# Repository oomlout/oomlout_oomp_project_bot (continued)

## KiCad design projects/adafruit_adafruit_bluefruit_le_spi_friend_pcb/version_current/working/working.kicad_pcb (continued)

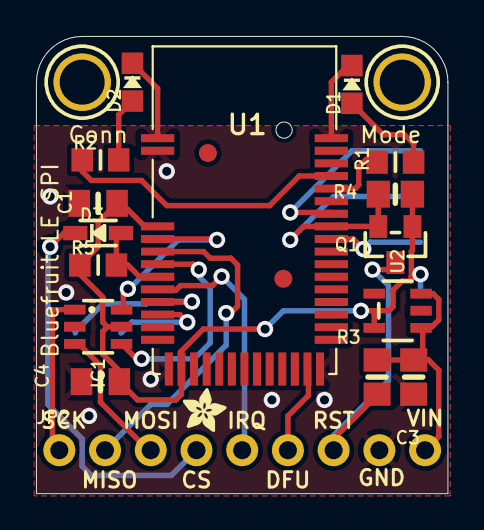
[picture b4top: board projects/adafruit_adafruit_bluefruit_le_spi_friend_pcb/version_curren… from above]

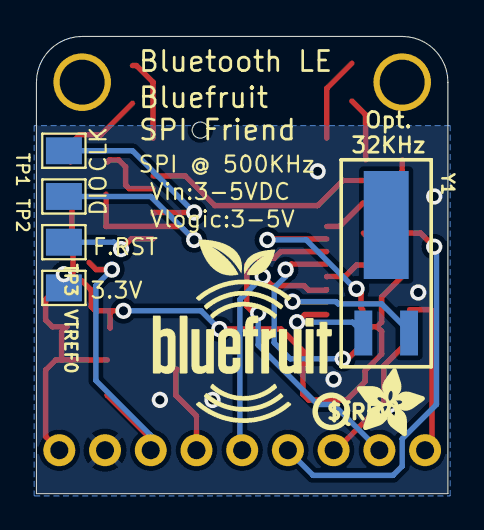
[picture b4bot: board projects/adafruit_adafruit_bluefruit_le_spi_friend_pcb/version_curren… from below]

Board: 2 copper layers, 22.9 x 25.4 mm, 29 parts (8 on the bottom side), 22 nets.

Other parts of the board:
U$3: ADAFRUIT_2.5MM
U$9: BLUEFRUITLOGO_100MM
U$17: ADAFRUIT_3.5MM
U$18: PCBFEAT-REV-040

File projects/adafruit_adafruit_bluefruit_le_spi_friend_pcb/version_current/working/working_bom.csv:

Row,Description,Part,References,Value,Footprint,Quantity Per PCB,Status,Datasheet
1,,CAP_CERAMIC0805_10MGAP,C1,1uF,0805_10MGAP,1, ,
2,,CAP_CERAMIC0805-NOOUTLINE,C3,10uF,0805-NO,1, ,
3,,CAP_CERAMIC0805_10MGAP,C4,10uF,0805_10MGAP,1, ,
4,,DIODESOD-323,D3,1N4148,SOD-323,1, ,
5,,LED0805_NOOUTLINE,D2,BLUE,CHIPLED_0805_NOOUTLINE,1, ,
6,,LED0805_NOOUTLINE,D1,RED,CHIPLED_0805_NOOUTLINE,1, ,
7,,74LVC2G34DBVR,IC1,74LVC2G34DBVR,SOT23-6,1, ,
8,,HEADER-1X970MIL,JP2,HEADER-1X970MIL,1X09_ROUND_70,1, ,
9,,MOSFET-NWIDE,Q1,BSS138,SOT23-WIDE@1,1, ,
10,,RESISTOR_0805MP,R1 R2,2K,_0805MP,2, ,
11,,RESISTOR0805_NOOUTLINE,R3 R4,100K,0805-NO,2, ,
12,,RESISTOR_0805MP,R5,100K,_0805MP,1, ,
13,,NRF51822_MODULE_MDBT40,U1,32KB NRF51822,BLE_MODULE_RAYTAC_MDBT40,1, ,
14,,VREG_SOT23-5,U2,MIC5225-3.3,SOT23-5,1, ,
15,,CRYSTAL2.0X6.0_32.768,Y1,32.768kHz (535-9166-2-ND),CRYSTAL_CYL_2X6MM_SMT,1, ,





Project info:
Schematic:,working
Variant:,default
Revision:,
Date:,2023-08-02_17-08-32
KiCad Version:,7.0.6-7.0.6~ubuntu22.04.1
Statistics:
Component Groups:,15
Component Count:,17 (0 SMD/ 0 THT)
Fitted Components:,17 (0 SMD/ 0 THT)
Number of PCBs:,1
Total Components:,17

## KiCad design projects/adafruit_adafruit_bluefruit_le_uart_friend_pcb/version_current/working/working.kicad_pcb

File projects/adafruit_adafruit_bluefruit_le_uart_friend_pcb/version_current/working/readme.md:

# OOMP Project  
## Adafruit-Bluefruit-LE-UART-Friend-PCB  by adafruit  
  
oomp key: oomp_projects_flat_adafruit_adafruit_bluefruit_le_uart_friend_pcb  
(snippet of original readme)  
  
- Adafruit Bluefruit LE UART Friend PCB  
<a href="http://www.adafruit.com/products/2479"><br/>  
Click here to purchase one from the Adafruit shop</a>  
  
The Bluefruit LE UART Friend makes it easy to add Bluetooth Low Energy connectivity to anything with a hardware or software serial port. We even have nice hardware flow control so you won't have to think about losing data. Connect to your Arduino or other microcontroller or even just a standard FTDI cable for debugging and testing.  
  
This multi-function module can do quite a lot! For most people, they'll be very happy to use the standard Nordic UART RX/TX connection profile. In this profile, the Bluefruit acts as a data pipe, that can 'transparently' transmit back and forth from your iOS or Android device. You can use our iOS App or Android App, or write your own to communicate with the UART service.  
  
PCB files for Adafruit Bluefruit LE UART Friend. Format is EagleCAD.   
- https://www.adafruit.com/product/2479  
  
--- License  
  
Adafruit invests time and resources providing this open source design, please support Adafruit and open-source hardware by purchasing products from [Adafruit](https://www.adafruit.com)!  
  
All text above must be included in any redistribution  
  
Designed by Limor Fried/Ladyada for Adafruit Industries.  
Creative Commons Attribution/Share-Alike, all text above must be included in any redistribution.   
See license.txt for additional information.  
  
  full source readme at [readme_src.md](readme_src.md)  
  
source repo at: [https://github.com/adafruit/Adafruit-Bluefruit-LE-UART-Friend-PCB](https://github.com/adafruit/Adafruit-Bluefruit-LE-UART-Friend-PCB)  
## Board  

## Schematic  

[schematic pdf](working_schematic.pdf)  
## Images

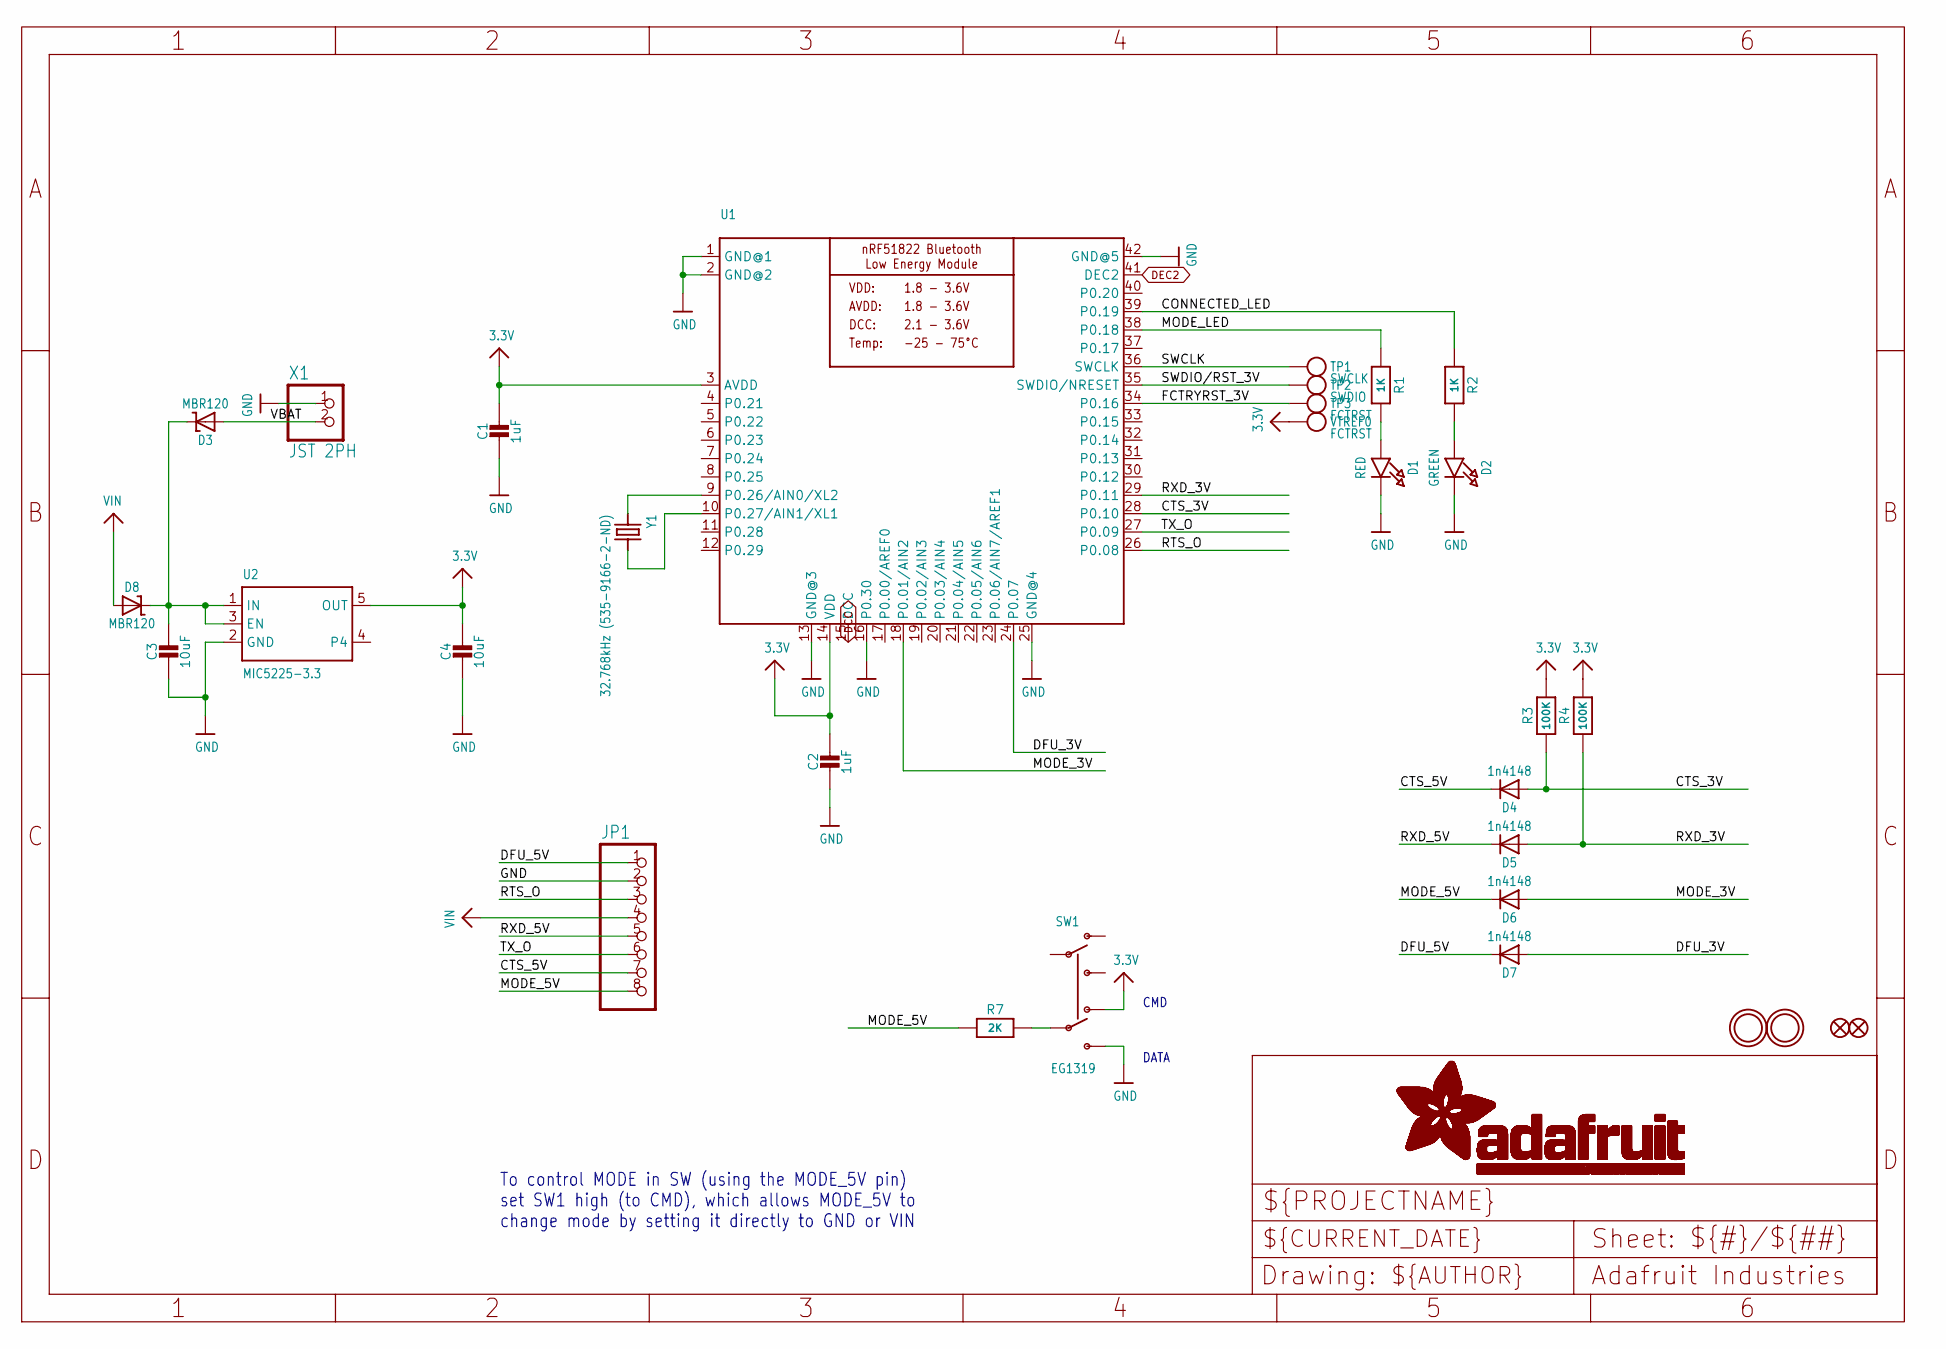
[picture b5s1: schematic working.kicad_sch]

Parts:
C1, C2: 1uF; 0805-NO
C3, C4: 10uF; 0805-NO
D1: RED; CHIPLED_0805_NOOUTLINE
D2: GREEN; CHIPLED_0805_NOOUTLINE
D3, D8: MBR120; SOD-123
D4, D5, D6, D7: 1n4148; SOD-323
FID1, FID2: FIDUCIAL""; FIDUCIAL_1MM
JP1: HEADER-1X876MIL; 1X08_ROUND_76
R1, R2: 1K; 0805-NO
R3, R4: 100K; 0805-NO
R7: 2K; 0805-NO
SW1: EG1319; EG1390
TP1: SWCLK; PAD-1.5X2.0
TP2: SWDIO; PAD-1.5X2.0
TP3: FCTRST; PAD-1.5X2.0
U1: NRF51822_MODULE_MDBT40; BLE_MODULE_RAYTAC_MDBT40
U2: MIC5225-3.3; SOT23-5
U$28, U$29: MOUNTINGHOLE2.5; MOUNTINGHOLE_2.5_PLATED
VTREF0: FCTRST; PAD-1.5X2.0
X1: JST 2PH; JSTPH2
Y1: 32.768kHz (535-9166-2-ND); CRYSTAL_CYL_2X6MM_SMT

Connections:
3.3V: C1.1, C2.1, C4.1, R3.2, R4.2, SW1.O2, U1.3 (AVDD), U1.14 (VDD), U2.5 (OUT), VTREF0.P$1
CONNECTED_LED: R2.1, U1.39 (P0.19)
CTS_3V: D4.A, R3.1, U1.28 (P0.10)
CTS_5V: D4.C, JP1.7
DCC: U1.15 (DCC)
DEC2: U1.41 (DEC2)
DFU_3V: D7.A, U1.24 (P0.07)
DFU_5V: D7.C, JP1.1
FCTRYRST_3V: TP3.P$1, U1.34 (P0.16)
GND: C1.2, C2.2, C3.2, C4.2, D1.C, D2.C, JP1.2, SW1.S2, U1.1 (GND@1), U1.2 (GND@2), U1.13 (GND@3), U1.16 (P0.30), U1.25 (GND@4), U1.42 (GND@5), U2.2 (GND), X1.1
MODE_3V: D6.A, U1.18 (P0.01/AIN2)
MODE_5V: D6.C, JP1.8, R7.1
MODE_LED: R1.1, U1.38 (P0.18)
unnamed: U1.9 (P0.26/AIN0/XL2), Y1.1
unnamed: U1.10 (P0.27/AIN1/XL1), Y1.2
unnamed: C3.1, D3.C, D8.C, U2.1 (IN), U2.3 (EN)
unnamed: R7.2, SW1.P2
unnamed: D1.A, R1.2
unnamed: D2.A, R2.2
RTS_O: JP1.3, U1.26 (P0.08)
RXD_3V: D5.A, R4.1, U1.29 (P0.11)
RXD_5V: D5.C, JP1.5
SWCLK: TP1.P$1, U1.36 (SWCLK)
SWDIO/RST_3V: TP2.P$1, U1.35 (SWDIO/NRESET)
TX_O: JP1.6, U1.27 (P0.09)
VBAT: D3.A, X1.2
VIN: D8.A, JP1.4

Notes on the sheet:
To control MODE in SW (using the MODE_5V pin) set SW1 high (to CMD), which allows MODE_5V to change mode by setting it directly to GND or VIN
CMD
DATA

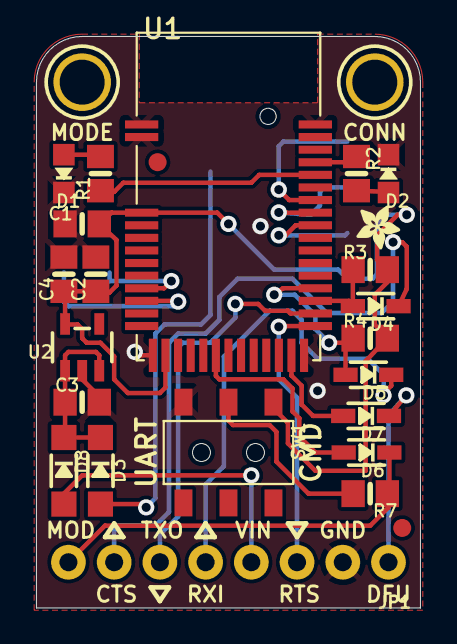
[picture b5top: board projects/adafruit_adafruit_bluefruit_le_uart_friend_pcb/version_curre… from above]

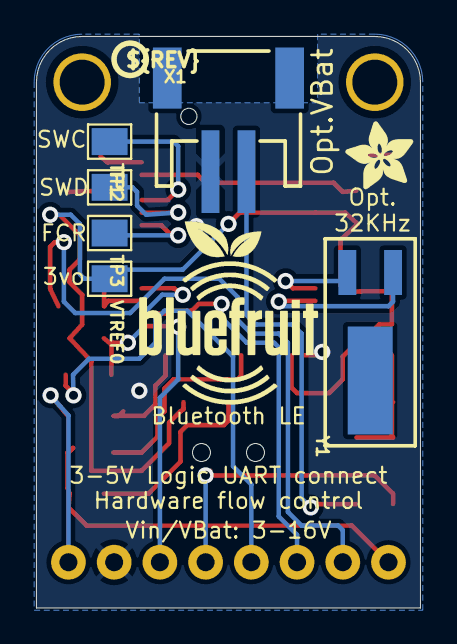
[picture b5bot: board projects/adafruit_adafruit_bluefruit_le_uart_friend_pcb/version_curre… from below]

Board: 2 copper layers, 21.3 x 31.8 mm, 35 parts (9 on the bottom side), 25 nets.

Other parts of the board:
U$9: BLUEFRUITLOGO_100MM
U$24: PCBFEAT-REV-040
U$25: ADAFRUIT_3.5MM
U$26: ADAFRUIT_2.5MM

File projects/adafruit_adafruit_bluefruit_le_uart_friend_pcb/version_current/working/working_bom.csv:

Row,Description,Part,References,Value,Footprint,Quantity Per PCB,Status,Datasheet
1,,CAP_CERAMIC0805-NOOUTLINE,C1 C2,1uF,0805-NO,2, ,
2,,CAP_CERAMIC0805-NOOUTLINE,C3 C4,10uF,0805-NO,2, ,
3,,DIODESOD-323,D4 D5 D6 D7,1n4148,SOD-323,4, ,
4,,LED0805_NOOUTLINE,D2,GREEN,CHIPLED_0805_NOOUTLINE,1, ,
5,,DIODE-SCHOTTKYSOD-123,D3 D8,MBR120,SOD-123,2, ,
6,,LED0805_NOOUTLINE,D1,RED,CHIPLED_0805_NOOUTLINE,1, ,
7,,HEADER-1X876MIL,JP1,HEADER-1X876MIL,1X08_ROUND_76,1, ,
8,,RESISTOR0805_NOOUTLINE,R1 R2,1K,0805-NO,2, ,
9,,RESISTOR0805_NOOUTLINE,R7,2K,0805-NO,1, ,
10,,RESISTOR0805_NOOUTLINE,R3 R4,100K,0805-NO,2, ,
11,,SWITCH_DPDTEG1390,SW1,EG1319,EG1390,1, ,
12,,VREG_SOT23-5,U2,MIC5225-3.3,SOT23-5,1, ,
13,,NRF51822_MODULE_MDBT40,U1,NRF51822_MODULE_MDBT40,BLE_MODULE_RAYTAC_MDBT40,1, ,
14,,CON_JST_PH_2PIN,X1,JST 2PH,JSTPH2,1, ,
15,,CRYSTAL2.0X6.0_32.768,Y1,32.768kHz (535-9166-2-ND),CRYSTAL_CYL_2X6MM_SMT,1, ,





Project info:
Schematic:,working
Variant:,default
Revision:,
Date:,2023-08-02_17-08-32
KiCad Version:,7.0.6-7.0.6~ubuntu22.04.1
Statistics:
Component Groups:,15
Component Count:,23 (0 SMD/ 0 THT)
Fitted Components:,23 (0 SMD/ 0 THT)
Number of PCBs:,1
Total Components:,23

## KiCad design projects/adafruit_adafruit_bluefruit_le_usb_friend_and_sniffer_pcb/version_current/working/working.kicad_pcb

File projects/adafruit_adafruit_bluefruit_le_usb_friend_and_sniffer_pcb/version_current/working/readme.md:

# Adafruit-Bluefruit-LE-USB-Friend-and-Sniffer-PCB by adafruit  
This is a harvested standardized copy of a project from github.  
The original project can be found at:  
https://github.com/adafruit/Adafruit-Bluefruit-LE-USB-Friend-and-Sniffer-PCB  
Please consult that link for additional, details, files, and license information.  
Note: It was auto harvested and if the original repo had more than one board file or anything out of the ordinary the files here are likely not representative.

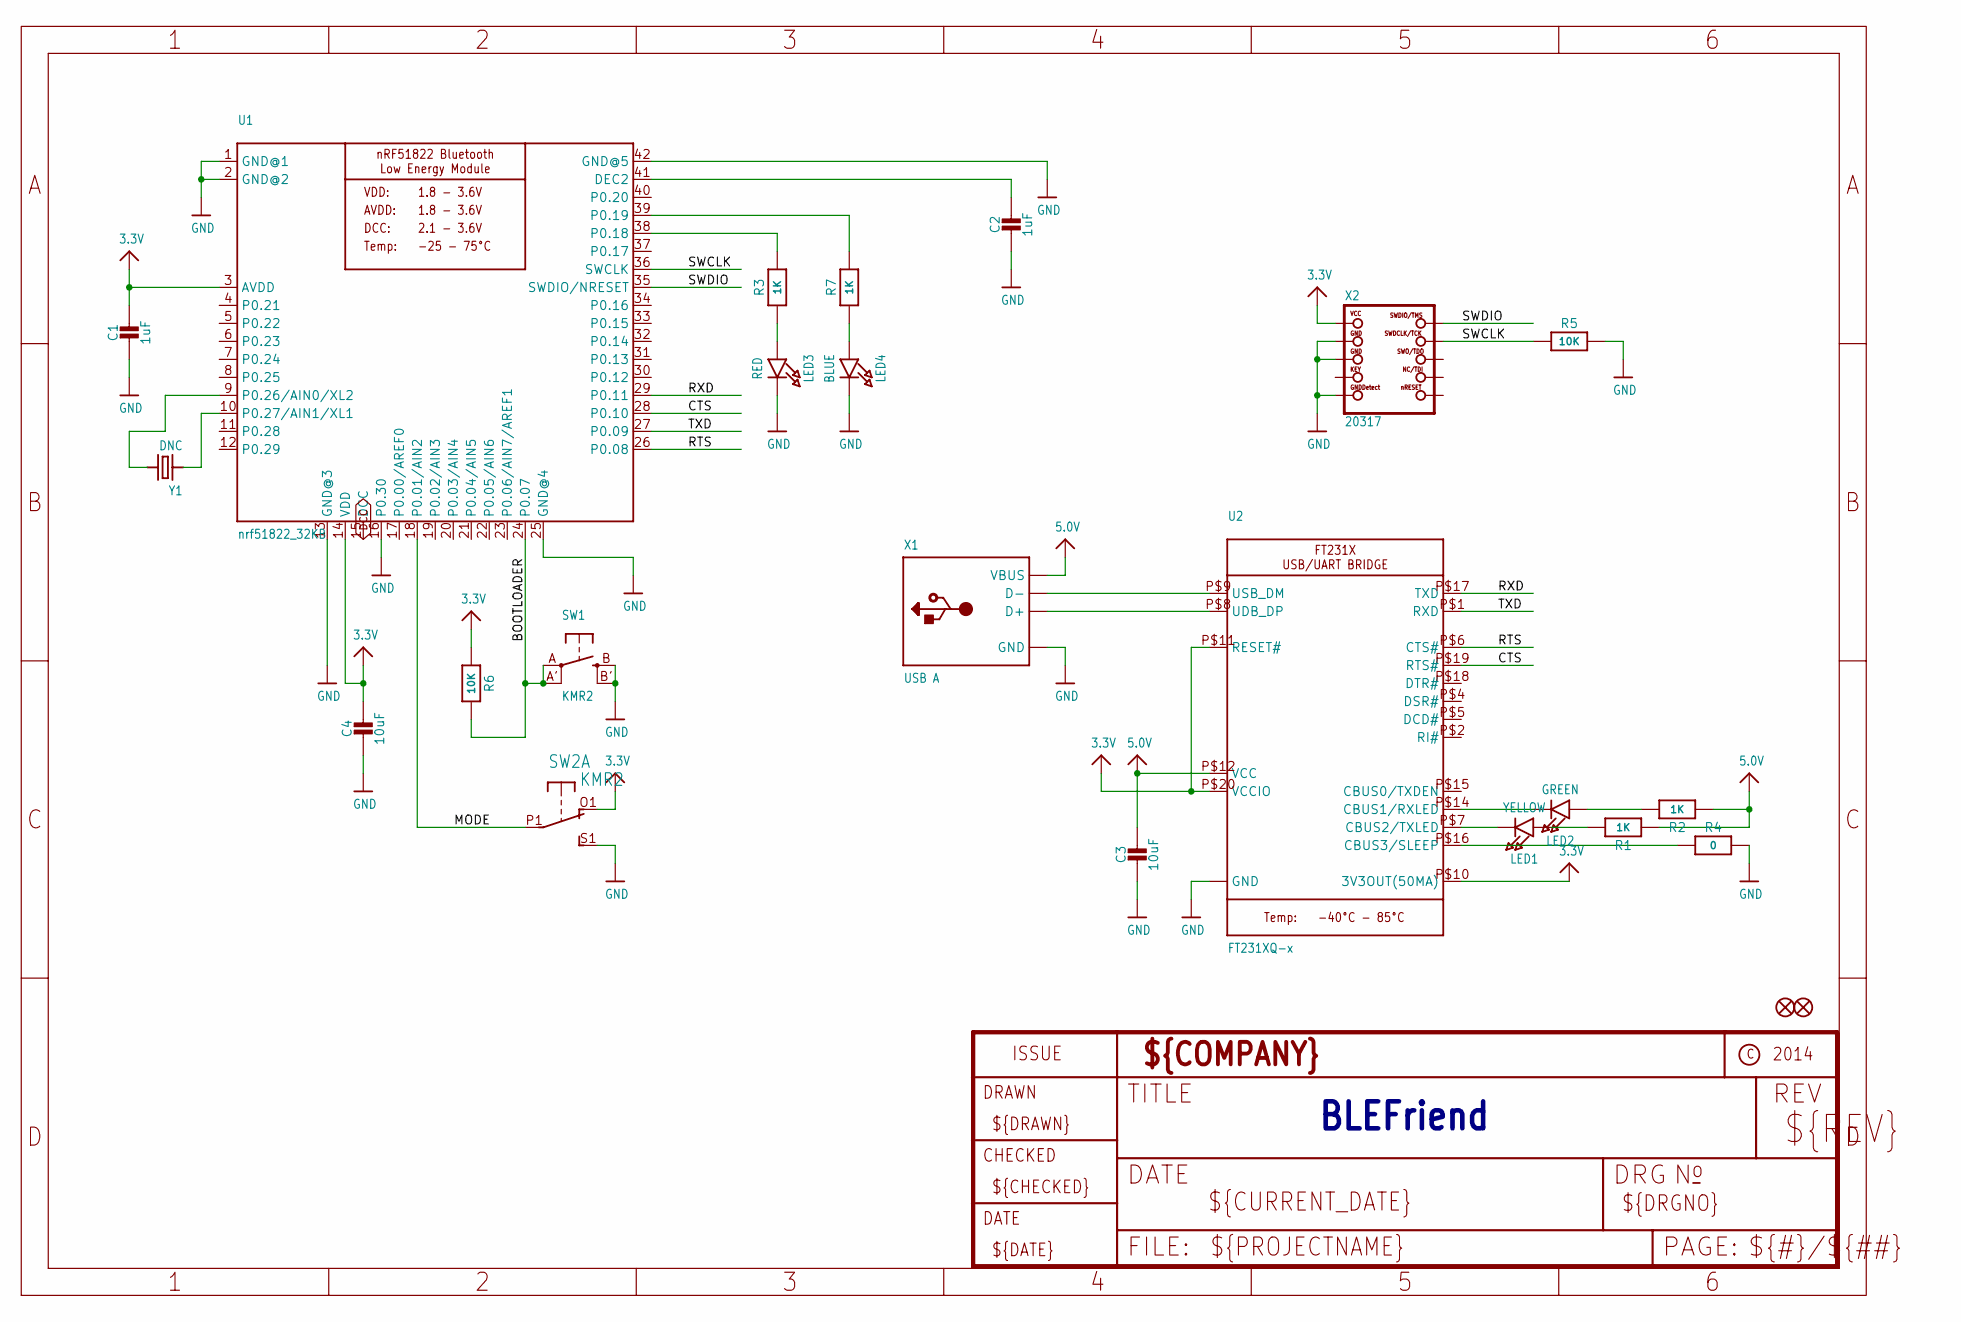
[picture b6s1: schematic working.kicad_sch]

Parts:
C1, C2: 1uF; _0805MP
C3, C4: 10uF; _0805MP
FID1, FID2: FIDUCIAL""; FIDUCIAL_1MM
LED1: YELLOW; CHIPLED_0805_NOOUTLINE
LED2: GREEN; CHIPLED_0805_NOOUTLINE
LED3: RED; CHIPLED_0805_NOOUTLINE
LED4: BLUE; CHIPLED_0805_NOOUTLINE
R1, R2, R3, R7: 1K; _0805MP
R4: 0; _0805MP
R5, R6: 10K; _0805MP
SW1: KMR2; BTN_KMR2_4.6X2.8
SW2: KMR2; EG1390
U1: nrf51822_32KB; BLE_MODULE_RAYTAC_MDBT40
U2: FT231XQ-x; QFN20_4MM
X1: USB A; USB_A-THM
X2: 20317; 2X05_1.27MM_BOX_POSTS
Y1: DNC; CRYSTAL_CYL_2X6MM_SMT

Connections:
3.3V: C1.1, C4.1, R6.1, SW2.O1 (O), U1.3 (AVDD), U1.14 (VDD), U2.P$10 (3V3OUT(50MA)), U2.P$11 (RESET#), U2.P$20 (VCCIO), X2.1 (VCC)
5.0V: C3.1, R1.1, R2.1, U2.P$12 (VCC), X1.VBUS
BOOTLOADER: R6.2, SW1.A, SW1.A' (P1), U1.24 (P0.07)
CTS: U1.28 (P0.10), U2.P$19 (RTS#)
DCC: U1.15 (DCC)
GND: C1.2, C2.2, C3.2, C4.2, LED3.C, LED4.C, R4.2, R5.2, SW1.B (S), SW1.B' (S1), SW2.S1 (S), U1.1 (GND@1), U1.2 (GND@2), U1.13 (GND@3), U1.16 (P0.30), U1.25 (GND@4), U1.42 (GND@5), U2.P$3 (GND), U2.P$13 (GND), U2.P$21 (GND), X1.GND, X2.3 (GND@1), X2.5 (GND@2), X2.9 (GNDDETECT)
MODE: SW2.P1, U1.18 (P0.01/AIN2)
unnamed: LED2.A, R2.2
unnamed: C2.1, U1.41 (DEC2)
unnamed: LED3.A, R3.1
unnamed: LED1.A, R1.2
unnamed: LED1.C, U2.P$7 (CBUS2/TXLED)
unnamed: LED2.C, U2.P$14 (CBUS1/RXLED)
unnamed: R4.1, U2.P$16 (CBUS3/SLEEP)
unnamed: U2.P$8 (UDB_DP), X1.D+
unnamed: U2.P$9 (USB_DM), X1.D-
unnamed: R3.2, U1.38 (P0.18)
unnamed: R7.2, U1.39 (P0.19)
unnamed: LED4.A, R7.1
unnamed: U1.9 (P0.26/AIN0/XL2), Y1.2
unnamed: U1.10 (P0.27/AIN1/XL1), Y1.1
RTS: U1.26 (P0.08), U2.P$6 (CTS#)
RXD: U1.29 (P0.11), U2.P$17 (TXD)
SWCLK: R5.1, U1.36 (SWCLK), X2.4 (SWDCLK)
SWDIO: U1.35 (SWDIO/NRESET), X2.2 (SWDIO)
TXD: U1.27 (P0.09), U2.P$1 (RXD)

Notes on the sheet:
BLEFriend

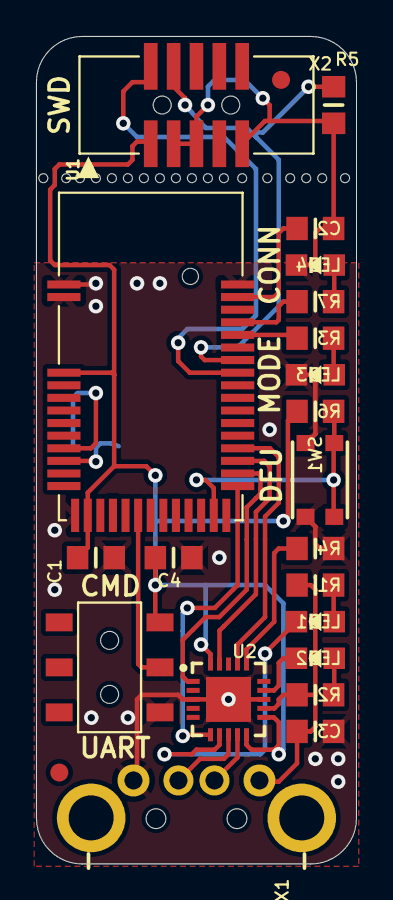
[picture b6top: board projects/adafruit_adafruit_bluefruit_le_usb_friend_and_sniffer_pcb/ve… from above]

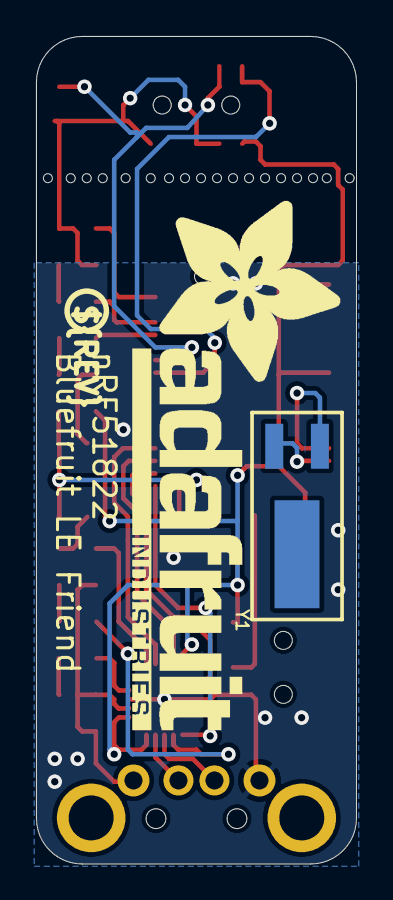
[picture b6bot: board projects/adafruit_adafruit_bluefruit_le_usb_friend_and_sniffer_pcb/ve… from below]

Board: 2 copper layers, 17.8 x 46.0 mm, 44 parts (3 on the bottom side), 25 nets.

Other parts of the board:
@HOLE0, @HOLE1, @HOLE2, @HOLE3, @HOLE4, @HOLE5, @HOLE6, @HOLE7, @HOLE8, @HOLE9, @HOLE10, @HOLE11, @HOLE12, @HOLE13, @HOLE14, @HOLE15, @HOLE16, @HOLE17: (no value)
U$22: ADAFRUIT_TEXT_30MM
U$27: PCBFEAT-REV-056

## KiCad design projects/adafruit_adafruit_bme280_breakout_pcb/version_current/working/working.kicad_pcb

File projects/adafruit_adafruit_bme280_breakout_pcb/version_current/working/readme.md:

# Adafruit-BME280-Breakout-PCB by adafruit  
This is a harvested standardized copy of a project from github.  
The original project can be found at:  
https://github.com/adafruit/Adafruit-BME280-Breakout-PCB  
Please consult that link for additional, details, files, and license information.  
Note: It was auto harvested and if the original repo had more than one board file or anything out of the ordinary the files here are likely not representative.

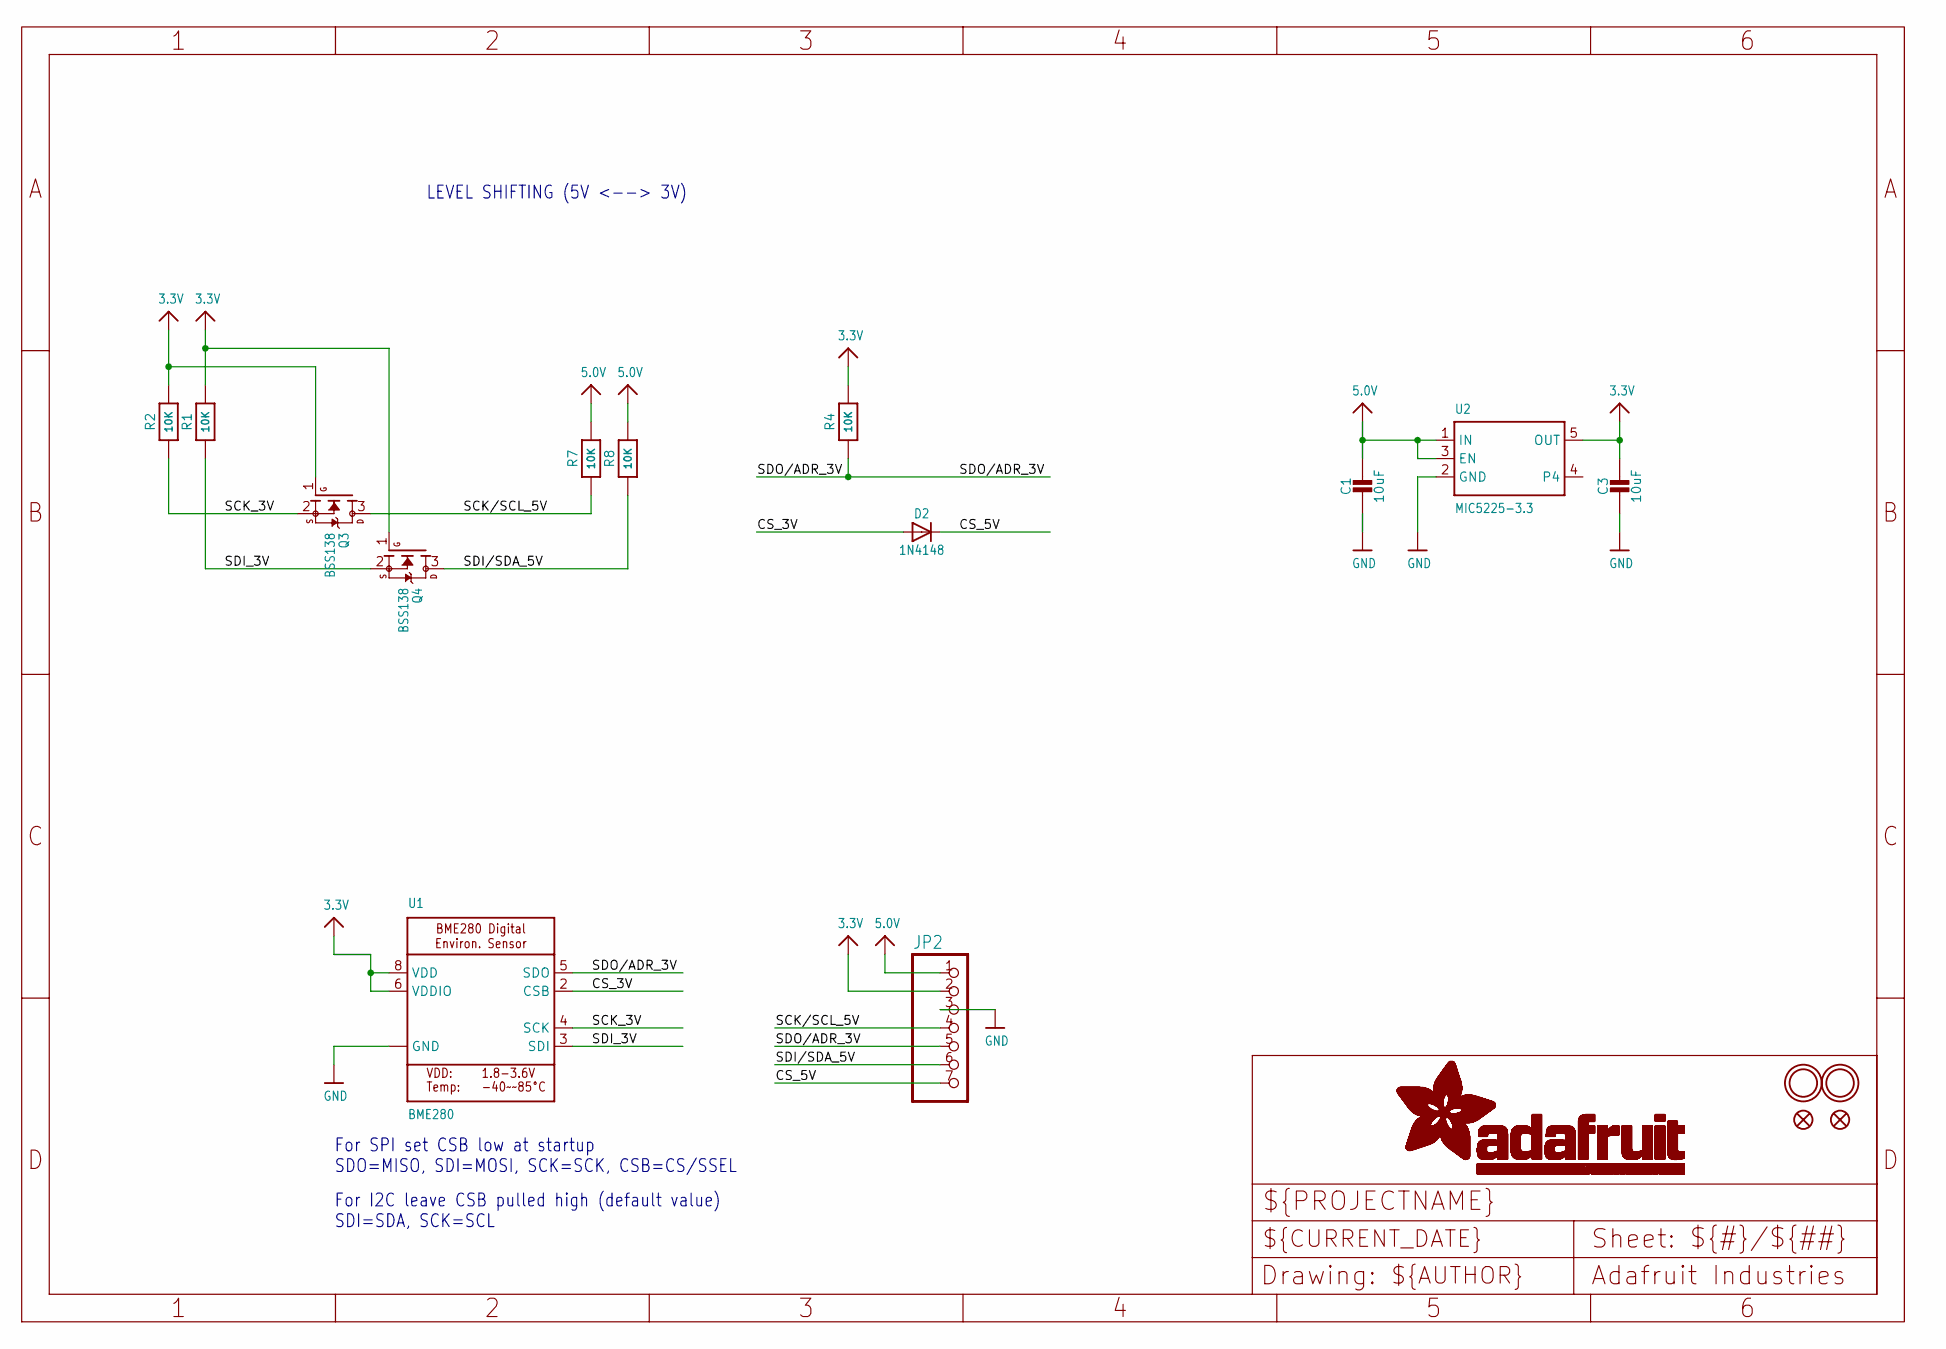
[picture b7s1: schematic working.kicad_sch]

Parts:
C1, C3: 10uF; 0805-NO
D2: 1N4148; SOD-323
JP2: HEADER-1X770MIL; 1X07_ROUND_70
Q3, Q4: BSS138; SOT23-WIDE
R1, R2, R7, R8: 10K; 0805-NO
R4: 10K; _0805MP
U1: BME280
U2: MIC5225-3.3; SOT23-5
U$5, U$15: FIDUCIAL""; FIDUCIAL_1MM
U$7, U$8: MOUNTINGHOLE2.0; MOUNTINGHOLE_2.0_PLATED

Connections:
3.3V: C3.1, JP2.2, Q3.1 (G), Q4.1 (G), R1.2, R2.2, R4.2, U1.6 (VDDIO), U1.8 (VDD), U2.5 (OUT)
5.0V: C1.1, JP2.1, R7.2, R8.2, U2.1 (IN), U2.3 (EN)
CS_3V: D2.A, U1.2 (CSB)
CS_5V: D2.C, JP2.7
GND: C1.2, C3.2, JP2.3, U1.1 (GND), U1.7 (GND), U2.2 (GND)
SCK/SCL_5V: JP2.4, Q3.3 (D), R7.1
SCK_3V: Q3.2 (S), R2.1, U1.4 (SCK)
SDI/SDA_5V: JP2.6, Q4.3 (D), R8.1
SDI_3V: Q4.2 (S), R1.1, U1.3 (SDI)
SDO/ADR_3V: JP2.5, R4.1, U1.5 (SDO)

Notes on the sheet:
LEVEL SHIFTING (5V <--> 3V)
For SPI set CSB low at startup SDO=MISO, SDI=MOSI, SCK=SCK, CSB=CS/SSEL
For I2C leave CSB pulled high (default value) SDI=SDA, SCK=SCL

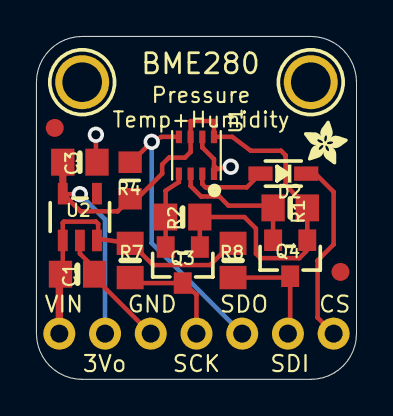
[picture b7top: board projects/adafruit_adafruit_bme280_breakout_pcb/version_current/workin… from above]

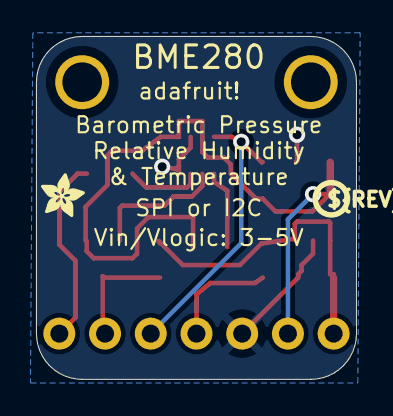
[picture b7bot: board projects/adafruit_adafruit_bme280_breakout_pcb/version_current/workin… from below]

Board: 2 copper layers, 17.8 x 19.0 mm, 20 parts (2 on the bottom side), 10 nets.

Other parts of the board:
U$2, U$6: ADAFRUIT_2.5MM
U$20: PCBFEAT-REV-040

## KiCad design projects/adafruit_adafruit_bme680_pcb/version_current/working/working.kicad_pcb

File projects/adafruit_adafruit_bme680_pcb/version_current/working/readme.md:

# OOMP Project  
## Adafruit-BME680-PCB  by adafruit  
  
oomp key: oomp_projects_flat_adafruit_adafruit_bme680_pcb  
(snippet of original readme)  
  
-- Adafruit BME680 PCB  
  
<a href="http://www.adafruit.com/products/3660"><br/>  
Click here to purchase one from the Adafruit shop</a>  
  
PCB files for the Adafruit BME680 Breakout. Format is EagleCAD schematic and board layout  
  
For more details, check out the product page at  
* https://www.adafruit.com/product/3660  
  
--- Description  
  
The long awaited BME680 from Bosch gives you all the environmental sensing you want in one small package. This little sensor contains temperature, humidity, barometric pressure, and VOC gas sensing capabilities. All over SPI or I2C at a great price!  
  
Like the BME280 & BMP280, this precision sensor from Bosch can measure humidity with ±3% accuracy, barometric pressure with ±1 hPa absolute accuracy, and temperature with ±1.0°C accuracy. Because pressure changes with altitude, and the pressure measurements are so good, you can also use it as an altimeter with  ±1 meter or better accuracy!  
  
The BME680 takes those sensors to the next step in that it contains a small MOX sensor. The heated metal oxide changes resistance based on the volatile organic compounds (VOC) in the air, so it can be used to detect gasses & alcohols such as Ethanol, Alcohol and Carbon Monoxide, and perform air quality measurements. Note it will give you one resistance value, with overall VOC content, but it cannot differentiate gasses or alcohols.  
  
Please note this sensor, like all VOC/gas sensors, has variability and to get precise me  
  full source readme at [readme_src.md](readme_src.md)  
  
source repo at: [https://github.com/adafruit/Adafruit-BME680-PCB](https://github.com/adafruit/Adafruit-BME680-PCB)  
## Board  

## Schematic  

[schematic pdf](working_schematic.pdf)  
## Images

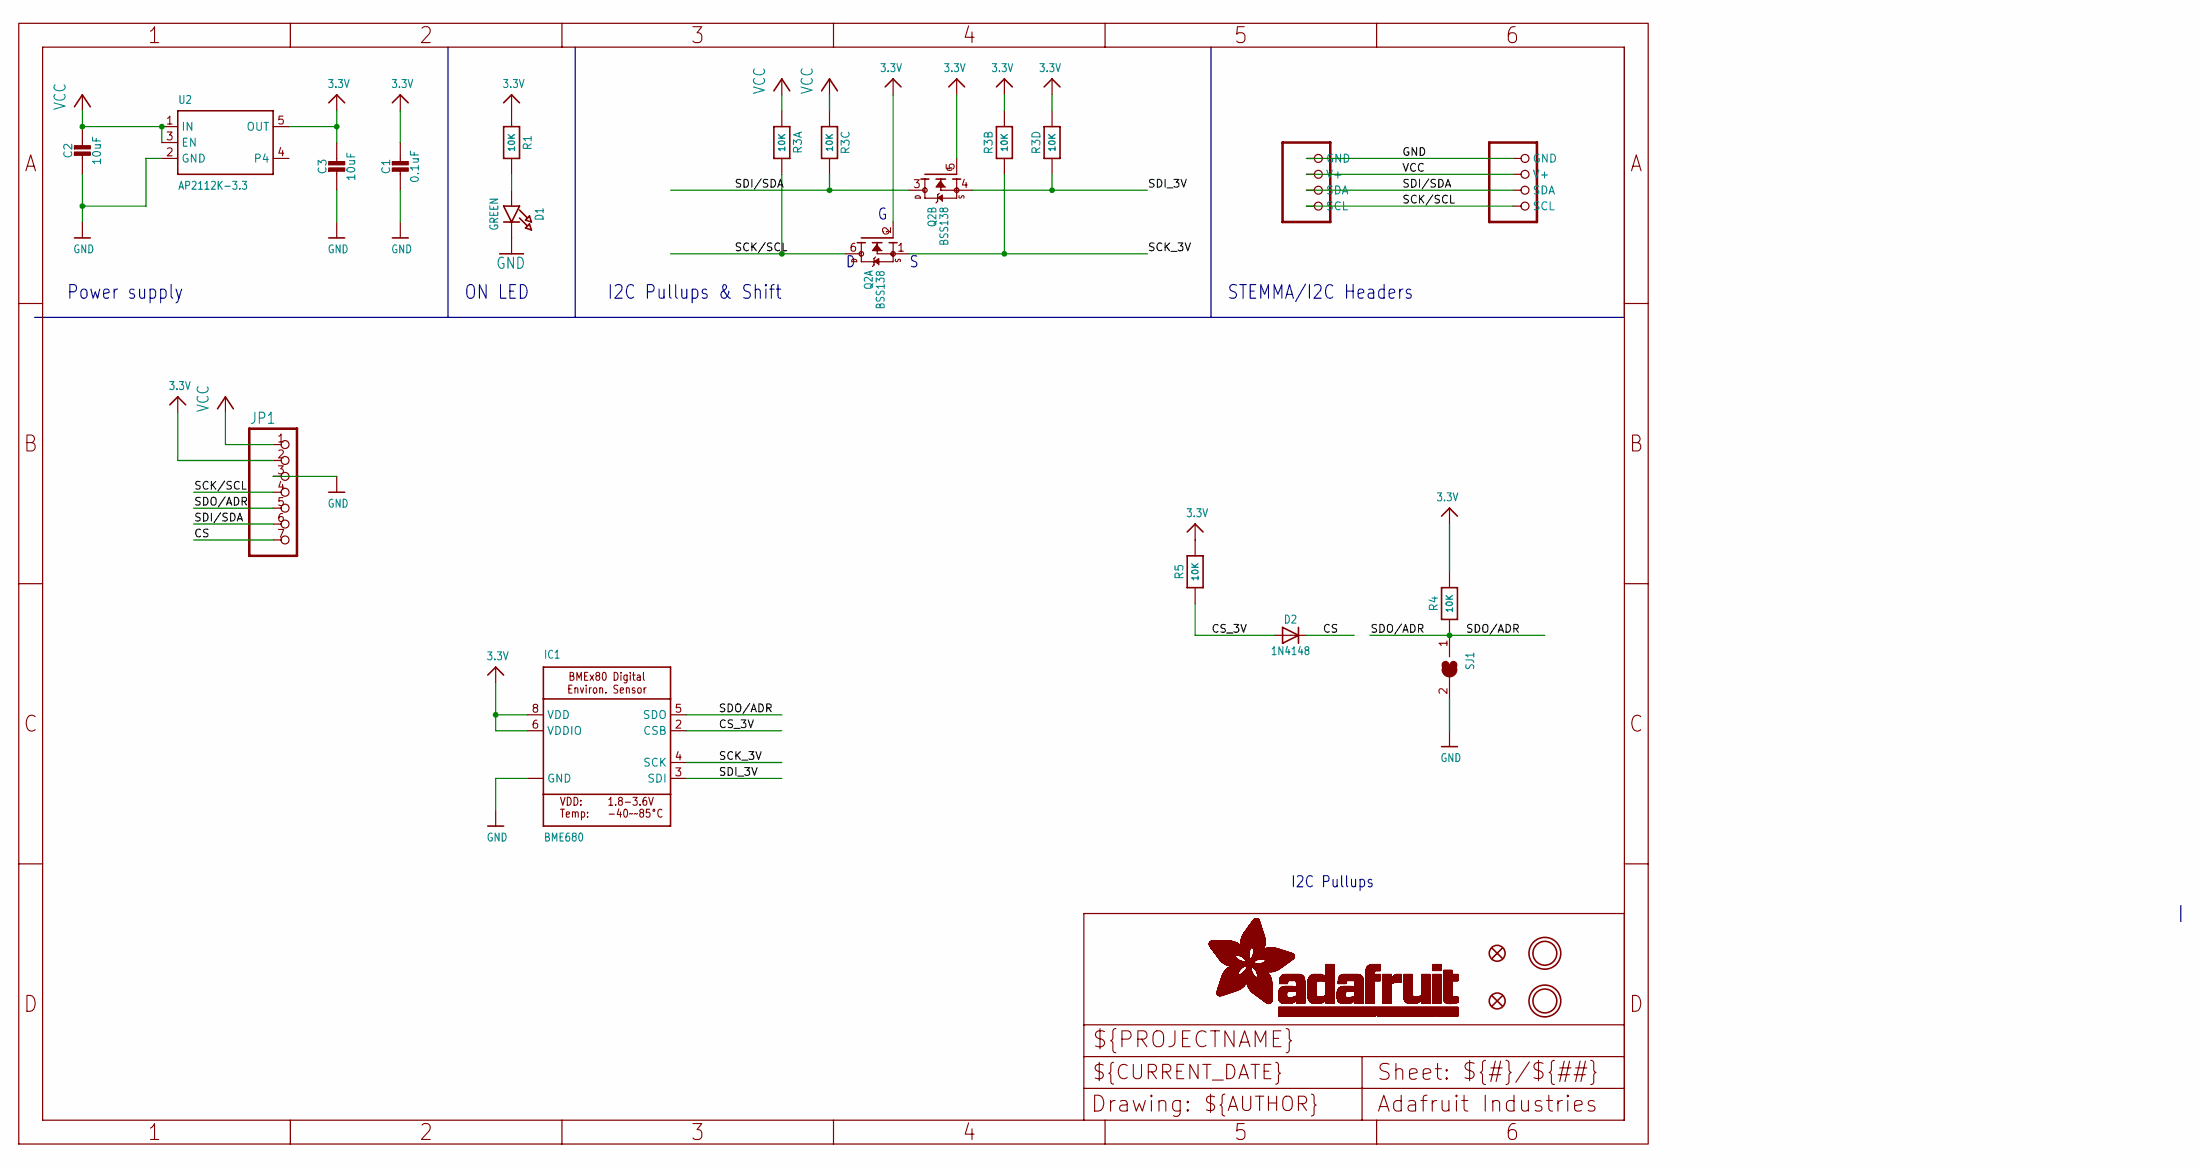
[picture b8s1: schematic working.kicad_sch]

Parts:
C1: 0.1uF; 0603-NO
C2, C3: 10uF; 0805-NO
CONN3, CONN4: STEMMA_I2C_QT; JST_SH4
D1: GREEN; CHIPLED_0603_NOOUTLINE
D2: 1N4148; SOD-323
FID3, FID4: FIDUCIAL_1MM
IC1: BME680
JP1: HEADER-1X770MIL; 1X07_ROUND_70
Q2: BSS138; SOT363
R1, R4, R5: 10K; 0603-NO
R3: 10K; RESPACK_4X0603
SJ1: SOLDERJUMPER; SOLDERJUMPER_ARROW_NOPASTE
U2: AP2112K-3.3; SOT23-5
U$1, U$17: MOUNTINGHOLE2.5; MOUNTINGHOLE_2.5_PLATED

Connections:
3.3V: C1.1, C3.1, IC1.6 (VDDIO), IC1.8 (VDD), JP1.2, Q2.2 (G), Q2.5 (G), R1.1, R3.2 (1), R3.4 (1), R4.2, R5.2, U2.5 (OUT)
CS: D2.C, JP1.7
CS_3V: D2.A, IC1.2 (CSB), R5.1
GND: C1.2, C2.2, C3.2, CONN3.1 (GND), CONN4.1 (GND), D1.C, IC1.1 (GND), IC1.7 (GND), JP1.3, SJ1.2, U2.2 (GND)
unnamed: D1.A, R1.2
SCK/SCL: CONN3.4 (SCL), CONN4.4 (SCL), JP1.4, Q2.6 (D), R3.8 (2)
SCK_3V: IC1.4 (SCK), Q2.1 (S), R3.7 (2)
SDI/SDA: CONN3.3 (SDA), CONN4.3 (SDA), JP1.6, Q2.3 (D), R3.6 (2)
SDI_3V: IC1.3 (SDI), Q2.4 (S), R3.5 (2)
SDO/ADR: IC1.5 (SDO), JP1.5, R4.1, SJ1.1
VCC: C2.1, CONN3.2 (V+), CONN4.2 (V+), JP1.1, R3.1, R3.3 (1), U2.1 (IN), U2.3 (EN)

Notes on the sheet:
ON LED
I2C Pullups
I2C Pullups & Shift
Power supply
STEMMA/I2C Headers

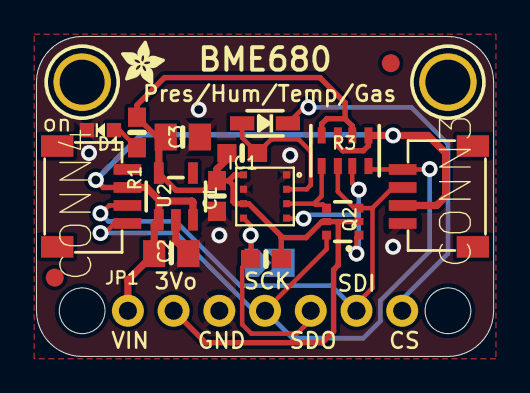
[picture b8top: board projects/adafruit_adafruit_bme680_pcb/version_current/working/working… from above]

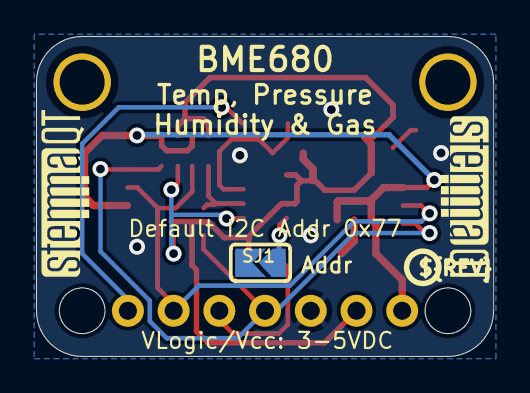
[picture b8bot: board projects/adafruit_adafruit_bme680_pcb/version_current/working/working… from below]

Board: 2 copper layers, 25.4 x 17.8 mm, 26 parts (4 on the bottom side), 11 nets.

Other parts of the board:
@HOLE0, @HOLE1: (no value)
U$4: ADAFRUIT_2.5MM
U$25: PCBFEAT-REV-040
U$30, U$31: STEMMAQT
